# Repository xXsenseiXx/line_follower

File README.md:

<<<<<<< Updated upstream
# line_follower
       _________
      /___   ___\
     //@@@\ /@@@\\
     \\@@@/ \@@@//
      \___ " ___/
         | - |
          \_/

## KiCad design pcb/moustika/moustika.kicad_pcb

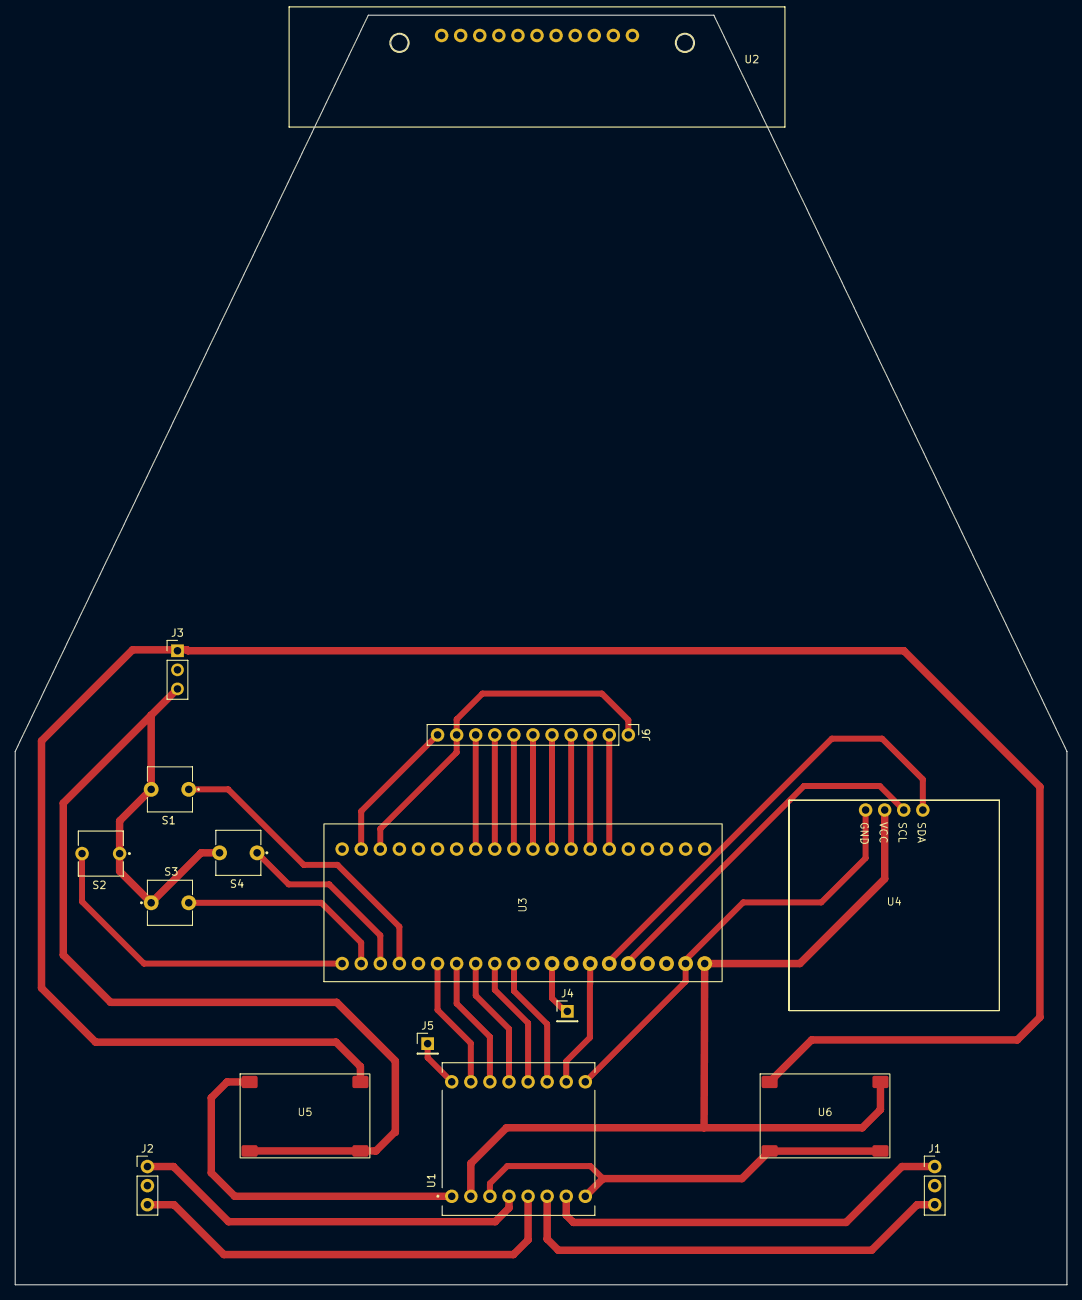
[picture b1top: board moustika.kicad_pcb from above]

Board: 2 copper layers, 140.0 x 169.0 mm, 16 parts (0 on the bottom side), 31 nets.

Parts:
J1, J2, J3: Conn_01x03_Socket; PinHeader_1x03_P2.54mm_Vertical
J4, J5: Conn_01x01_Socket; PinHeader_1x01_P2.54mm_Vertical
J6: Conn_01x11_Pin; PinHeader_1x11_P2.54mm_Vertical
S1, S2, S3, S4: BUTT-2; SW_BUTT-2
U1: ROB-14450; ROBO-14450
U2: QTR-8A
U3: stm32_black_pill
U4: SSD1308; SSD1803
U5, U6: mini360

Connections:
+3.3V: J6.1, J6.10, U1.2 (VCC), U3.20 (3V3), U3.23 (3V3), U4.2 (VCC), U6.1 (IN+)
+5V: U1.1 (VM), U5.4 (OUT+)
+8V: J3.1, U5.1 (IN+), U6.4 (OUT+)
GND: J3.3, S1.2, S2.1, S3.1, S4.2, U1.3 (GND), U1.8 (GND), U1.9 (GND), U3.19 (GND), U4.1 (GND), U5.2 (IN-), U5.3 (OUT-), U6.2 (IN-), U6.3 (OUT-)
unnamed: J1.1, U1.7 (B01)
unnamed: J1.3, U1.6 (B02)
unnamed: J2.1, U1.4 (A01)
unnamed: J2.3, U1.5 (A02)
unnamed: J4.1, U3.12 (B4)
unnamed: J5.1, U1.16 (PWMA)
unnamed: J6.2, U3.35 (A0)
unnamed: J6.3, U3.34 (A1)
unnamed: J6.4, U3.33 (A2)
unnamed: J6.5, U3.32 (A3)
unnamed: J6.6, U3.31 (A4)
unnamed: J6.7, U3.30 (A5)
unnamed: J6.8, U3.29 (A6)
unnamed: J6.9, U3.28 (A7)
unnamed: J6.11, U3.22 (GND)
unnamed: U1.14 (AI1), U3.7 (A10)
unnamed: U1.15 (AI2), U3.6 (A9)
unnamed: U1.12 (BI1), U3.9 (A12)
unnamed: U1.11 (BI2), U3.10 (A15)
unnamed: U1.10 (PWMB), U3.14 (B6)
unnamed: U1.13 (STBY), U3.8 (A11)
unnamed: U3.15 (B7), U4.4 (SDA)
unnamed: U3.16 (B8), U4.3 (SCL)
unnamed: S2.2, U3.1 (B12)
unnamed: S3.2, U3.2 (B13)
unnamed: S4.1, U3.3 (B14)
unnamed: S1.1, U3.4 (B15)

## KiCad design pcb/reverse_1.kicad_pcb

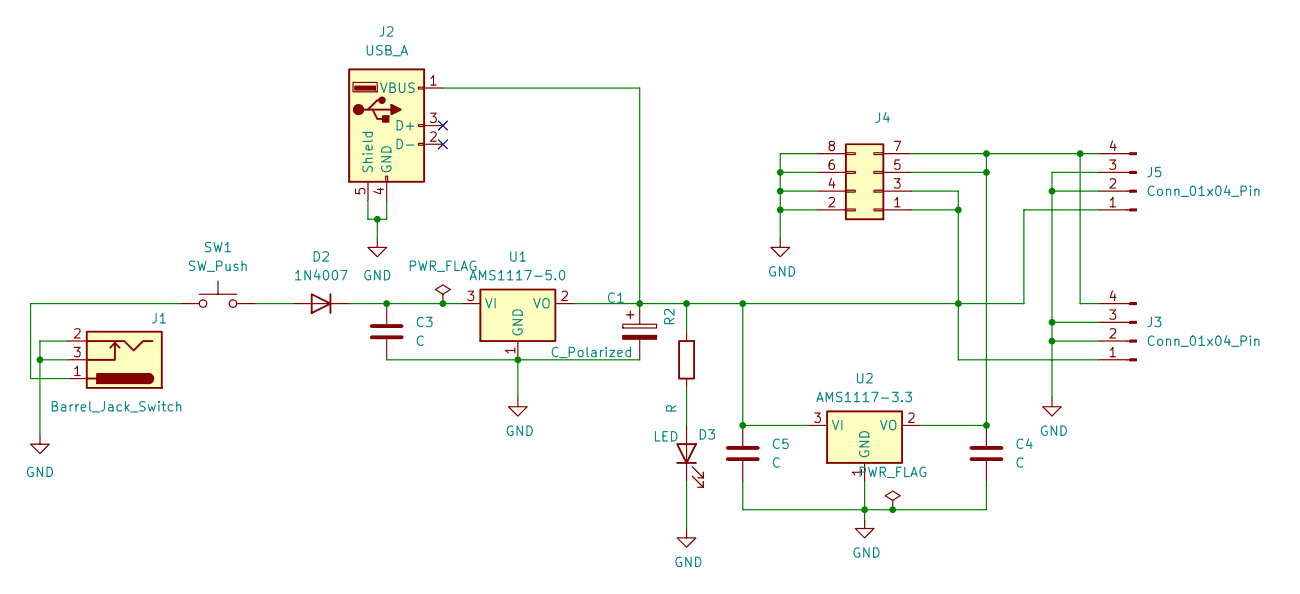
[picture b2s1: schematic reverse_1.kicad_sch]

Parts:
C1: C_Polarized; CP_Radial_D5.0mm_P2.50mm
C3, C4, C5: C; C_0805_2012Metric
D2: 1N4007; D_SOD-128
D3: LED; LED_D3.0mm
J1: Barrel_Jack_Switch; BarrelJack_Horizontal
J2: USB_A; USB_A_Molex_67643_Horizontal
J3, J5: Conn_01x04_Pin; PinHeader_1x04_P2.54mm_Vertical
J4: Conn_02x04_Odd_Even; PinHeader_2x04_P2.54mm_Vertical
R2: R; R_0805_2012Metric
SW1: SW_Push; SW_DIP_SPSTx01_Slide_6.7x4.1mm_W7.62mm_P2.54mm_LowProfile
U1: AMS1117-5.0; SOT-223-3_TabPin2
U2: AMS1117-3.3; SOT-223-3_TabPin2

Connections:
GND: C1.2, C3.2, C4.2, C5.2, D3.1 (K), J1.2, J1.3, J2.4 (GND), J2.5 (Shield), J3.2, J3.3, J4.2, J4.4, J4.6, J4.8, J5.2, J5.3, U1.1 (GND), U2.1 (GND)
unnamed: D2.2 (A), SW1.2
unnamed: C3.1, D2.1 (K), U1.3 (VI)
unnamed: D3.2 (A), R2.1
unnamed: J1.1, SW1.1
unnamed: C1.1, C5.1, J2.1 (VBUS), J3.1, J4.1, J4.3, J5.1, R2.2, U1.2 (VO), U2.3 (VI)
unnamed: C4.1, J3.4, J4.5, J4.7, J5.4, U2.2 (VO)

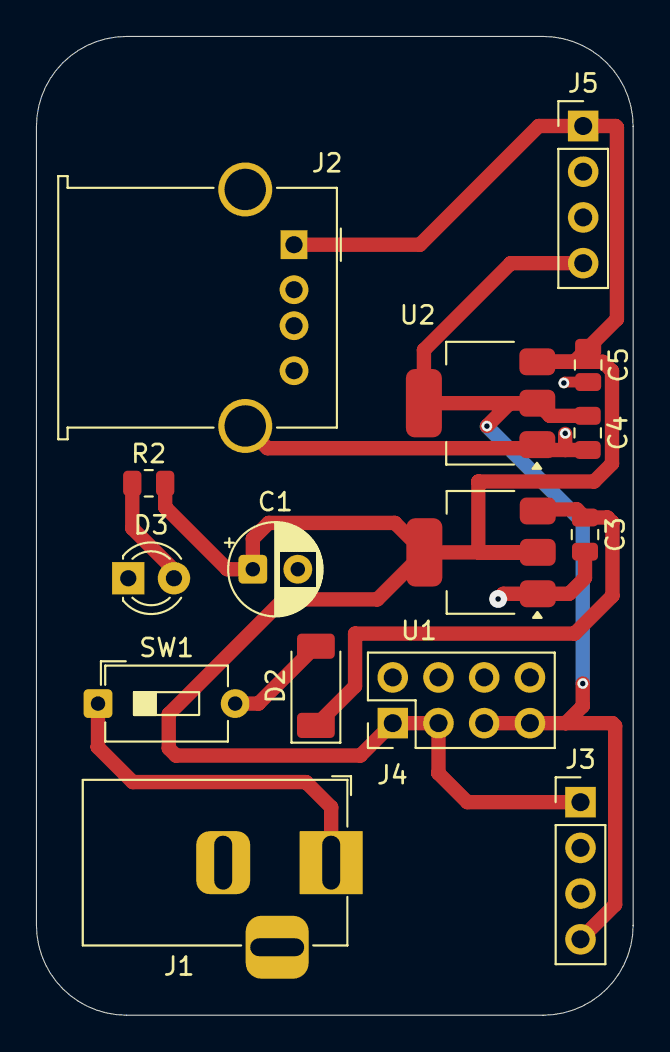
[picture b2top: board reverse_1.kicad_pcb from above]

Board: 2 copper layers, 33.1 x 54.4 mm, 15 parts (0 on the bottom side), 7 nets.

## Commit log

2026-02-04 init
2026-02-04 init2
2026-02-04 test
2026-02-04 trying to run the code
2026-02-04 final pcb
2026-02-04 changed the pads of the driver module footprint
2026-02-05 testtttt
2026-02-05 Auto stash before merge of "main" and "origin/main"
    changed stuffs
2026-02-05 heads
2026-02-05 headers final
2026-02-05 yasser
2026-02-05 uuuu
2026-02-05 brooo
2026-02-05 fixed the chassis
2026-02-06 moustica
2026-02-06 i did fix the qtr read value
2026-02-06 added pid
2026-02-06 code
2026-02-06 working
2026-02-06 the best code yet
2026-02-07 robust
2026-02-08 working calibration
2026-02-08 hamod 69
2026-02-09 pcb adjustment
